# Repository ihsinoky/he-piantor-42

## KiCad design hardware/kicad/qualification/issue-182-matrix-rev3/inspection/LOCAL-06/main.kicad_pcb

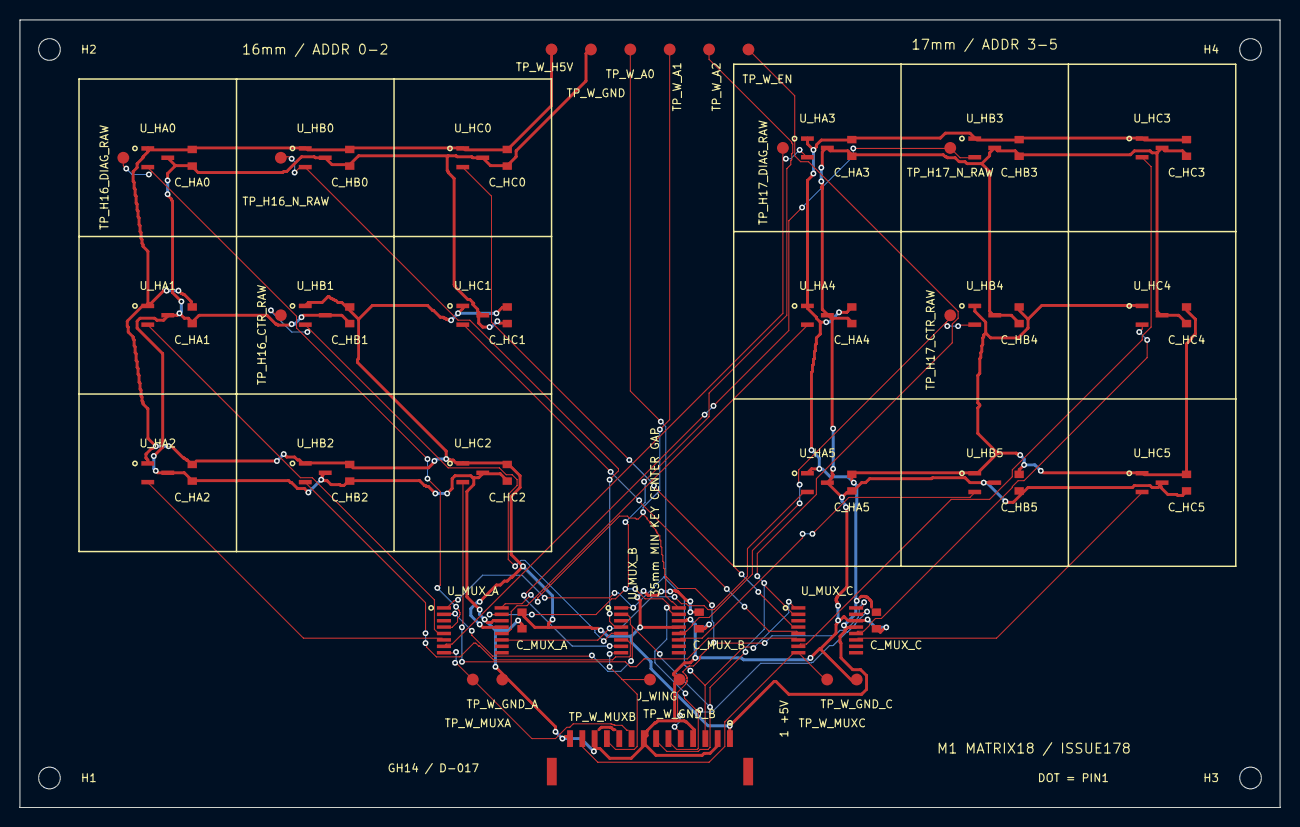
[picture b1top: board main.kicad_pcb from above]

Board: 2 copper layers, 128.0 x 80.0 mm, 65 parts (0 on the bottom side), 27 nets.

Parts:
C_HA0, C_HA1, C_HA2, C_HA3, C_HA4, C_HA5: GRM188R71C104KA01D; capacitor
C_HB0, C_HB1, C_HB2, C_HB3, C_HB4, C_HB5: GRM188R71C104KA01D; capacitor
C_HC0, C_HC1, C_HC2, C_HC3, C_HC4, C_HC5: GRM188R71C104KA01D; capacitor
C_MUX_A: GRM188R71C104KA01D; capacitor
C_MUX_B: GRM188R71C104KA01D; capacitor
C_MUX_C: GRM188R71C104KA01D; capacitor
H1, H2, H3, H4: NPTH_2.2mm; mounting
J_WING: BM14B-GHS-TBT(LF)(SN); connector
TP_H16_CTR_RAW, TP_H16_DIAG_RAW, TP_H16_N_RAW, TP_H17_CTR_RAW, TP_H17_DIAG_RAW, TP_H17_N_RAW: PCB_PAD_1.2MM; testpoint
TP_W_A0, TP_W_A1, TP_W_A2: PCB_PAD_1.2MM; testpoint
TP_W_EN: PCB_PAD_1.2MM; testpoint
TP_W_GND: PCB_PAD_1.2MM; testpoint
TP_W_GND_A: PCB_PAD_1.2MM; testpoint
TP_W_GND_B: PCB_PAD_1.2MM; testpoint
TP_W_GND_C: PCB_PAD_1.2MM; testpoint
TP_W_H5V: PCB_PAD_1.2MM; testpoint
TP_W_MUXA: PCB_PAD_1.2MM; testpoint
TP_W_MUXB: PCB_PAD_1.2MM; testpoint
TP_W_MUXC: PCB_PAD_1.2MM; testpoint
U_HA0, U_HA1, U_HA2, U_HA3, U_HA4, U_HA5: DRV5055A3QDBZR; hall
U_HB0, U_HB1, U_HB2, U_HB3, U_HB4, U_HB5: DRV5055A3QDBZR; hall
U_HC0, U_HC1, U_HC2, U_HC3, U_HC4, U_HC5: DRV5055A3QDBZR; hall
U_MUX_A: TMUX1208PWR; mux
U_MUX_B: TMUX1208PWR; mux
U_MUX_C: TMUX1208PWR; mux

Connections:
GND: C_HA0.2, C_HA1.2, C_HA2.2, C_HA3.2, C_HA4.2, C_HA5.2, C_HB0.2, C_HB1.2, C_HB2.2, C_HB3.2, C_HB4.2, C_HB5.2, C_HC0.2, C_HC1.2, C_HC2.2, C_HC3.2, C_HC4.2, C_HC5.2, C_MUX_A.2, C_MUX_B.2, C_MUX_C.2, J_WING.2, J_WING.4, J_WING.8, J_WING.10, J_WING.12, J_WING.14, TP_W_GND.1, TP_W_GND_A.1, TP_W_GND_B.1, TP_W_GND_C.1, U_HA0.3, U_HA1.3, U_HA2.3, U_HA3.3, U_HA4.3, U_HA5.3, U_HB0.3, U_HB1.3, U_HB2.3, U_HB3.3, U_HB4.3, U_HB5.3, U_HC0.3, U_HC1.3, U_HC2.3, U_HC3.3, U_HC4.3, U_HC5.3, U_MUX_A.14, U_MUX_B.14, U_MUX_C.14
HALL_5V: C_HA0.1, C_HA1.1, C_HA2.1, C_HA3.1, C_HA4.1, C_HA5.1, C_HB0.1, C_HB1.1, C_HB2.1, C_HB3.1, C_HB4.1, C_HB5.1, C_HC0.1, C_HC1.1, C_HC2.1, C_HC3.1, C_HC4.1, C_HC5.1, C_MUX_A.1, C_MUX_B.1, C_MUX_C.1, J_WING.1, TP_W_H5V.1, U_HA0.1, U_HA1.1, U_HA2.1, U_HA3.1, U_HA4.1, U_HA5.1, U_HB0.1, U_HB1.1, U_HB2.1, U_HB3.1, U_HB4.1, U_HB5.1, U_HC0.1, U_HC1.1, U_HC2.1, U_HC3.1, U_HC4.1, U_HC5.1, U_MUX_A.13, U_MUX_B.13, U_MUX_C.13
H_A0_RAW: TP_H16_DIAG_RAW.1, U_HA0.2, U_MUX_A.4
H_A1_RAW: U_HA1.2, U_MUX_A.5
H_A2_RAW: U_HA2.2, U_MUX_A.6
H_A3_RAW: TP_H17_DIAG_RAW.1, U_HA3.2, U_MUX_A.7
H_A4_RAW: U_HA4.2, U_MUX_A.12
H_A5_RAW: U_HA5.2, U_MUX_A.11
H_B0_RAW: TP_H16_N_RAW.1, U_HB0.2, U_MUX_B.4
H_B1_RAW: TP_H16_CTR_RAW.1, U_HB1.2, U_MUX_B.5
H_B2_RAW: U_HB2.2, U_MUX_B.6
H_B3_RAW: TP_H17_N_RAW.1, U_HB3.2, U_MUX_B.7
H_B4_RAW: TP_H17_CTR_RAW.1, U_HB4.2, U_MUX_B.12
H_B5_RAW: U_HB5.2, U_MUX_B.11
H_C0_RAW: U_HC0.2, U_MUX_C.4
H_C1_RAW: U_HC1.2, U_MUX_C.5
H_C2_RAW: U_HC2.2, U_MUX_C.6
H_C3_RAW: U_HC3.2, U_MUX_C.7
H_C4_RAW: U_HC4.2, U_MUX_C.12
H_C5_RAW: U_HC5.2, U_MUX_C.11
MUX_A0: J_WING.3, TP_W_A0.1, U_MUX_A.1, U_MUX_B.1, U_MUX_C.1
MUX_A1: J_WING.5, TP_W_A1.1, U_MUX_A.16, U_MUX_B.16, U_MUX_C.16
MUX_A2: J_WING.6, TP_W_A2.1, U_MUX_A.15, U_MUX_B.15, U_MUX_C.15
MUX_OUT_A: J_WING.9, TP_W_MUXA.1, U_MUX_A.8
MUX_OUT_B: J_WING.11, TP_W_MUXB.1, U_MUX_B.8
MUX_OUT_C: J_WING.13, TP_W_MUXC.1, U_MUX_C.8
WING_EN: J_WING.7, TP_W_EN.1, U_MUX_A.2, U_MUX_B.2, U_MUX_C.2

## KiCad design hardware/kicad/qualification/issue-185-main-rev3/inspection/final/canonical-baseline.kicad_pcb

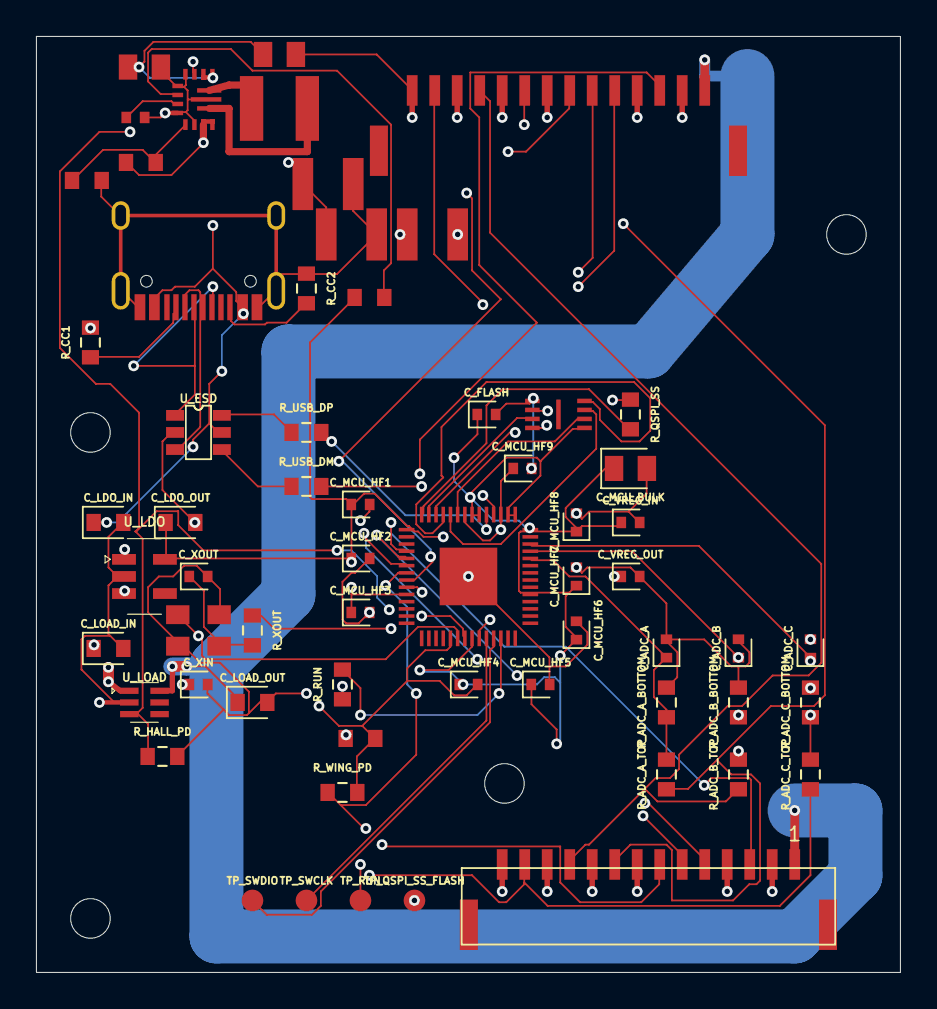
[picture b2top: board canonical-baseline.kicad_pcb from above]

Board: 4 copper layers, 48.0 x 52.0 mm, 66 parts (0 on the bottom side), 44 nets.

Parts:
C1: 15pF; C1
C2: 15pF; C2
C3: 100nF; C3
C4: 100nF; C4
C5: 100nF; C5
C6: 100nF; C6
C7: 100nF; C7
C8: 100nF; C8
C9: 100nF; C9
C10: 100nF; C10
C11: 100nF; C11
C12: 1uF; C12
C13: 1uF; C13
C14: 10uF; C14
C15: 100nF; C15
C16: 1uF; C16
C17: 1uF; C17
C18: 1uF; C18
C19: 1uF; C19
C20: 1nF; C20
C21: 1nF; C21
C22: 1nF; C22
C23: 22uF 16V X6S 0805; C23
C24: 22uF 16V X6S 0805; C24
C25: 100nF; C25
C26: 22uF 16V X7R 1210; C26
C27: 22uF 16V X7R 1210; C27
C28: 22uF 16V X7R 1210; C28
H1: NPTH_2.2mm; H1
H2: NPTH_2.2mm; H2
H3: NPTH_2.2mm; H3
H4: NPTH_2.2mm; H4
J1: TYPE-C-31-M-12; J1
J2: BM14B-GHS-TBT(LF)(SN); J2
J3: BM14B-GHS-TBT(LF)(SN); J3
L1: 1.5uH XFL4020-152MEC; L1
R1: 5.1k; R1
R2: 5.1k; R2
R3: 27; R3
R4: 27; R4
R5: 1k; R5
R6: 100k; R6
R7: 100k; R7
R8: 10k; R8
R9: 1k; R9
R10: 6.8k; R10
R11: 10k; R11
R12: 6.8k; R12
R13: 10k; R13
R14: 6.8k; R14
R15: 10k; R15
R16: 100k; R16
R17: 54.9k 0.1% 25ppm/K; R17
R18: 10k 0.1% 25ppm/K; R18
R19: 100k; R19
TP1: TestPoint; TP1
TP2: TestPoint; TP2
TP3: TestPoint; TP3
TP4: TestPoint; TP4
U1: RP2040; U1
U2: USBLC6-2SC6; U2
U3: W25Q16JVUXIQ; U3
U4: AP2112K-3.3TRG1; U4
U5: TPS22919DCKR; U5
U6: TPS63070RNMR; U6
Y1: ABM8-272-T3; Y1

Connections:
ADC_A: C20.1, R10.2, R11.1, U1.38
ADC_B: C21.1, R12.2, R13.1, U1.39
ADC_C: C22.1, R14.2, R15.1, U1.40
CC1: J1.3, R1.1
CC2: J1.10, R2.1
FB_5V2: R17.2, R18.1, U6.5
GND: C1.2, C2.2, C3.2, C4.2, C5.2, C6.2, C7.2, C8.2, C9.2, C10.2, C11.2, C12.2, C13.2, C14.2, C15.2, C16.2, C17.2, C18.2, C19.2, C20.2, C21.2, C22.2, C23.2, C24.2, C25.2, C26.2, C27.2, C28.2, J1.1, J1.12, J1.13, J2.2, J2.4, J2.8, J2.10, J2.12, J2.14, J3.2, J3.4, J3.8, J3.10, J3.12, J3.14, R1.2, R2.2, R6.2, R7.2, R11.2, R13.2, R15.2, R16.2, R18.2, U1.19, U1.57, U2.2, U3.4, U4.2, U5.2, U6.1, U6.4, U6.6, U6.10, U6.15, Y1.2, Y1.4
HALL_5V: C19.1, J2.1, J3.1, U5.6
HALL_PWR_EN: R7.1, U1.9, U5.3, U6.14
MUX_A0: J2.3, J3.3, U1.4
MUX_A1: J2.5, J3.5, U1.5
MUX_A2: J2.6, J3.6, U1.6
MUX_EN1: J3.7, R16.1, U1.8
MUX_OUT_A: J2.9, J3.9, R10.1
MUX_OUT_B: J2.11, J3.11, R12.1
MUX_OUT_C: J2.13, J3.13, R14.1
QSPI_SCLK: U1.52, U3.6
QSPI_SD0: U1.53, U3.5
QSPI_SD1: U1.55, U3.2
QSPI_SD2: U1.54, U3.3
QSPI_SD3: U1.51, U3.7
QSPI_SS_FLASH: R5.2, TP4.1, U3.1
QSPI_SS_MCU: R5.1, U1.56
RAIL_PG: R19.2, U6.2
RUN: R8.2, TP3.1, U1.26
SW1: L1.1, U6.11
SW2: L1.2, U6.9
SWCLK: TP2.1, U1.24
SWDIO: TP1.1, U1.25
USB_DM: R4.2, U1.46
USB_DM_CONN: J1.5, J1.8, U2.3
USB_DM_ESD: R4.1, U2.4
USB_DP: R3.2, U1.47
USB_DP_CONN: J1.4, J1.9, U2.1
USB_DP_ESD: R3.1, U2.6
V1V1: C11.1, C13.1, U1.23, U1.45, U1.50
V3V3: C3.1, C4.1, C5.1, C6.1, C7.1, C8.1, C9.1, C10.1, C12.1, C14.1, C15.1, C17.1, R8.1, R19.1, U1.1, U1.10, U1.22, U1.33, U1.42, U1.43, U1.44, U1.48, U1.49, U3.8, U4.5
V5V2: C26.1, C27.1, C28.1, R17.1, U5.1, U6.7, U6.8
VAUX: C25.1, U6.3
VBUS: C16.1, C18.1, C23.1, C24.1, J1.2, J1.11, U2.5, U4.1, U4.3, U6.12, U6.13
WING_EN: J2.7, R6.1, U1.7
XIN: C1.1, U1.20, Y1.1
XOUT: R9.2, U1.21
XOUT_XTAL: C2.1, R9.1, Y1.3
